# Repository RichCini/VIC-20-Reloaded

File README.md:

# VIC-20-Reloaded
Reimaging of the original VIC-20cr ("cost-reduced") main board in a smaller footprint based
on schmetics of the 251027-01D version as redrawn by Steve Gray. This should represent
changes through ECO 830151 as of 4/12/1983.

## Introduction
This project is a re-implementation of a VIC-20 based on the cost-reduced version from 1983.
It's built using commonly-existing TTL (all of the original types of chips used are still 
generally available) and original core chips from a VIC-20 (the CPU, VIAs, VIC, and original
mask ROMs) which were typically socketed. The memory chips (2114L and 6116), which are not
typically socketed, are still available as used or new-old-stock. 

## How is this version similar?
Since it's based on the original schematics, it's identical operationally and 99% identical
electrically (except as noted in the next section). I also tried to keep the parts placement
relationally similar to the original, recognizing that the board size is different. Parts 
designators are the same.

## How is this version different?
### Size
My main goal was to reimplement the VIC in a smaller form factor. I was able to squeeze it
{mostly} into an S-100 format (which is 10" x 5"; actual is 10.375" x 5.375") size. As such,
this board isn't a drop-in replacement. However, the spacing and placement of the side 
(power/joystick) and the rear (expansion cartridge, video, serial IEC) are
placed at the correct distances from the upper-right corner.

### Ports
Due to the smaller form factor, the cassette port was eliminated (instead opting for a 
6-pin header for an external driver) and the user port was moved to the left side. The 
orientation of the expansion connector was changed to vertical (more like the Atari 2600
which saved about 2" of board space). Using the expansion connector is limited to one
cartridge, or an expansion board that uses two pieces connected by a cable (there is
another repro here that has an example).

### Power
Electrically, I opted for a single 5V power supply (9VAC wasn't needed as there is no
cassette port), and the power switch is slightly different due to parts availability.
The main fuse holder is different, but the same 5x20mm fuse is used. Large axial
capacitor was replaced with smaller radial cap of the same value.

### Other
Since the board is autorouted to a smaller footprint, circuit paths and keepout
areas are different from the original.

## Versions
* v1.0-001: Initial prototype based on original schematic; screen artifacts
* v1.1-001: Second prototype with a rearranged chip layout; screen artifacts.
* v1.1-002: Third prototype. A transcription error was found in the original schematic.  
            Corrected. Works.
* v1.1-002E: Final version.

## Known Bugs
Current Release (1.1-002E):
* The signal flag "S01" was incorrectly used for the CPU PHI1 output. The system works
  with this improperly connected signal, but the fix is to lift pins UE10.3 and UC3.3
  and connect them with a jumper. The way the traces are routed make it hard to make a
  single-cut fix.

Prior Release (1.1-002D): 
* An error was introduced in this version as a result of rearranging the data bus lines
  lines on IC UF8 (74LS245). D4 (pin 4) and D5 (pin 5) were reversed. There is a picture
  (ECO_001) which indicates a convenient place to cut two traces and cross-wire them.
  Will be fixed in the next version.

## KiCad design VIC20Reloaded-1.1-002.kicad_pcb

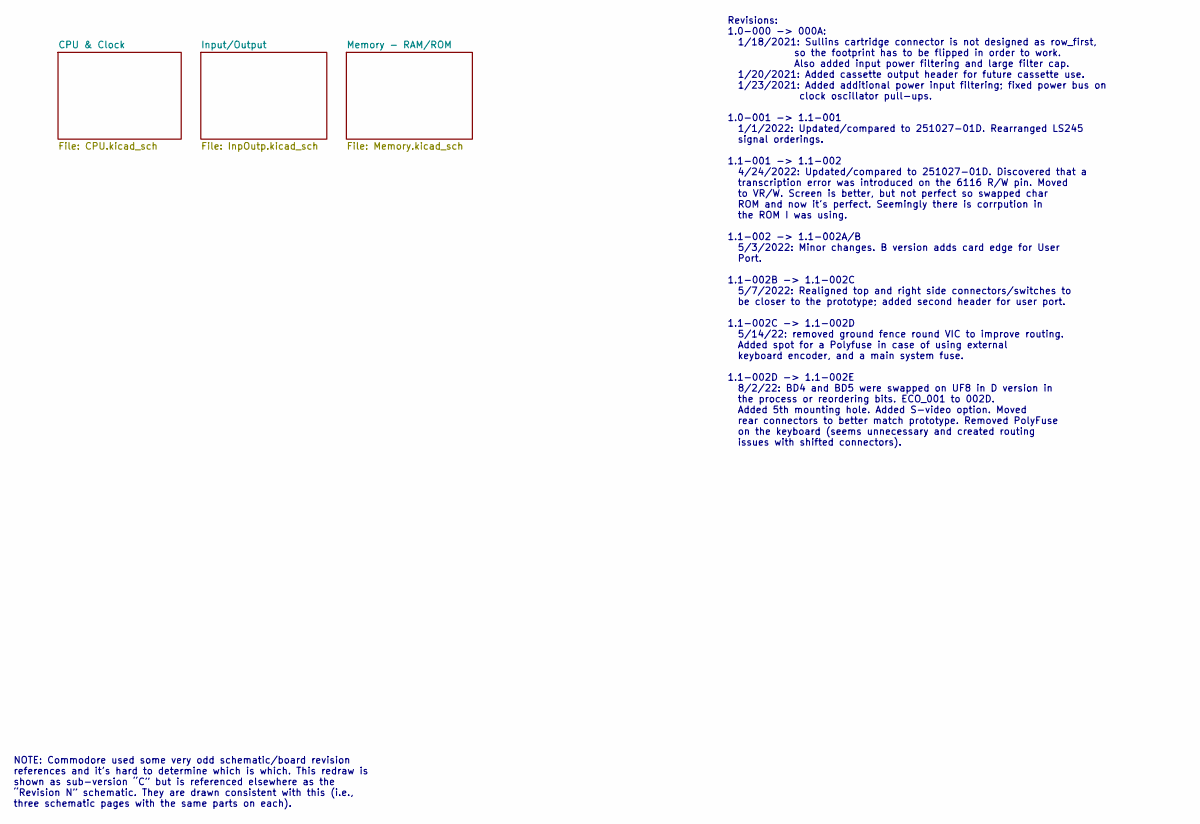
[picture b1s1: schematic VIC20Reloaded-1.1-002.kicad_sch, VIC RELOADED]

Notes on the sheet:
NOTE: Commodore used some very odd schematic/board revision references and it’s hard to determine which is which. This redraw is shown as sub-version “C” but is referenced elsewhere as the “Revision N” schematic. They are drawn consistent with this (i.e., three schematic pages with the same parts o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
Revisions: 1.0-000 -> 000A: 1/18/2021: Sullins cartridge connector is not designed as row_first, so the footprint has to be flipped in order to work. Also added input power filtering and large filter cap. 1/20/2021: Added cassette output header for future cassette use. 1/23/2021: Added additional p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

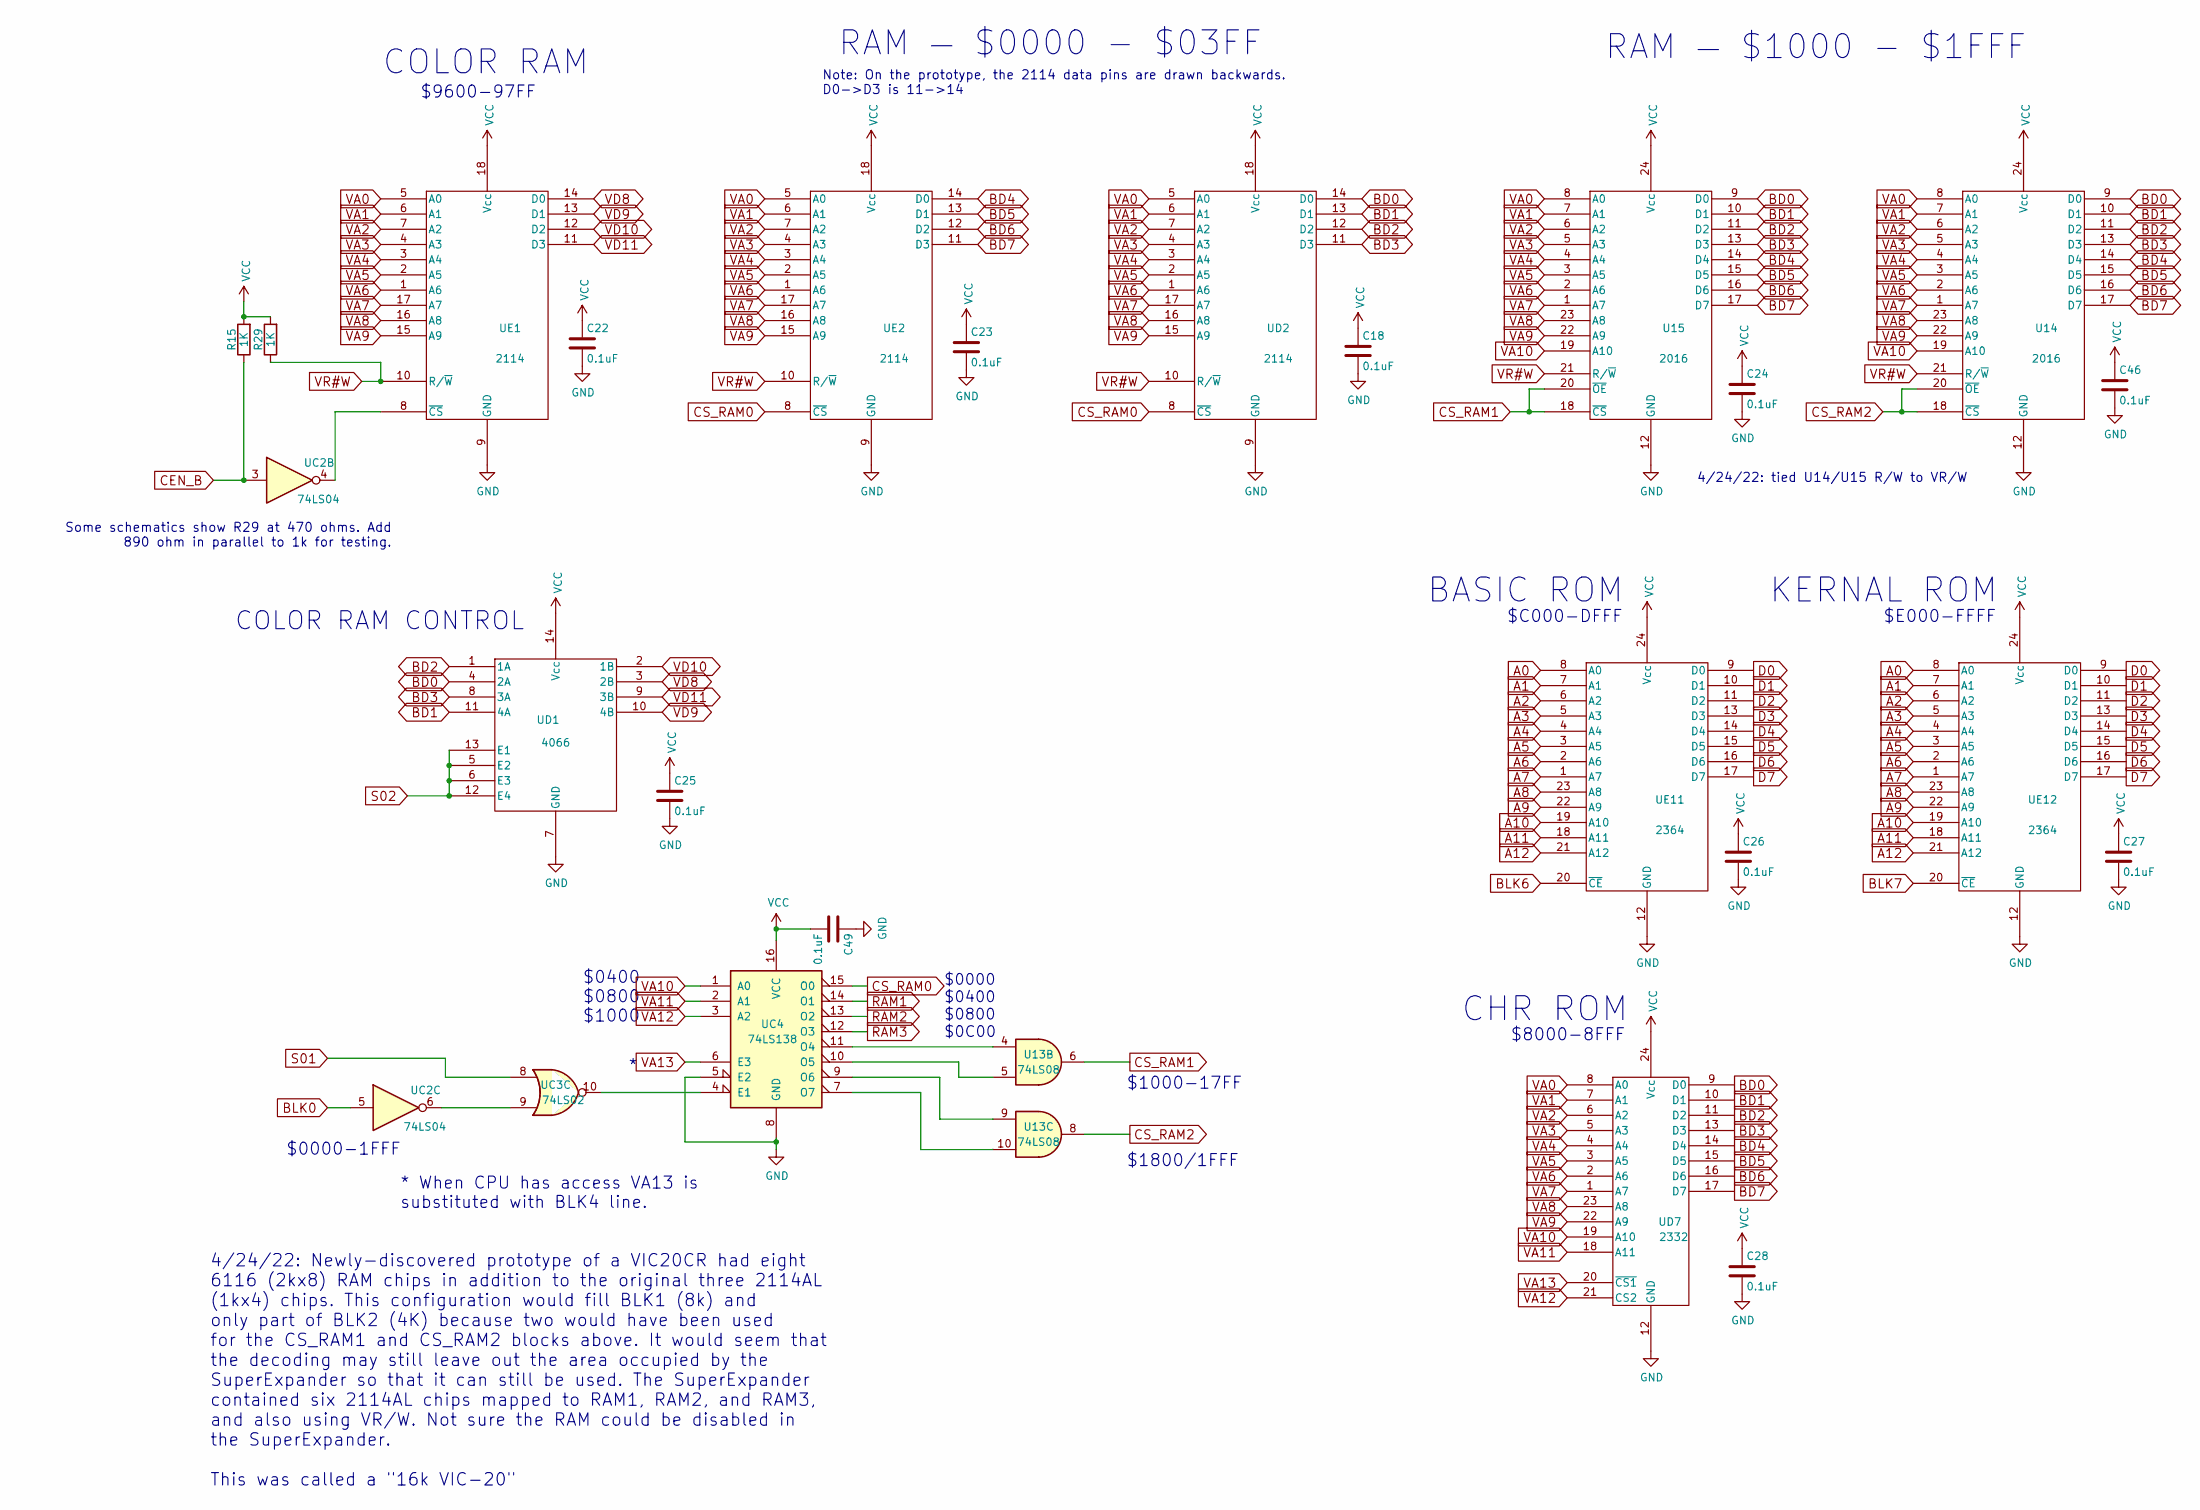
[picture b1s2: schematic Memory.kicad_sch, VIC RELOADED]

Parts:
C18, C22, C23, C24, C25, C26, C27, C28, C46, C49: 0.1uF; C_Disc_D4.3mm_W1.9mm_P5.00mm
R15, R29: 1K; R_Axial_DIN0207_L6.3mm_D2.5mm_P7.62mm_Horizontal
U13: 74LS08; DIP-14_W7.62mm_Socket
U14, U15: 2016; DIP-24_W15.24mm_Socket
UC2: 74LS04; DIP-14_W7.62mm_Socket
UC3: 74LS02; DIP-14_W7.62mm_Socket
UC4: 74LS138; DIP-16_W7.62mm_Socket
UD1: 4066; DIP-14_W7.62mm_Socket
UD2: 2114; DIP-18_W7.62mm_Socket
UD7: 2332; DIP-24_W15.24mm_Socket
UE1, UE2: 2114; DIP-18_W7.62mm_Socket
UE11, UE12: 2364; DIP-24_W15.24mm_Socket

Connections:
A0: UE11.8 (A0), UE12.8 (A0); also elsewhere on the board
A1: UE11.7 (A1), UE12.7 (A1); also elsewhere on the board
A2: UE11.6 (A2), UE12.6 (A2); also elsewhere on the board
A3: UE11.5 (A3), UE12.5 (A3); also elsewhere on the board
A4: UE11.4 (A4), UE12.4 (A4); also elsewhere on the board
A5: UE11.3 (A5), UE12.3 (A5); also elsewhere on the board
A6: UE11.2 (A6), UE12.2 (A6); also elsewhere on the board
A7: UE11.1 (A7), UE12.1 (A7); also elsewhere on the board
A8: UE11.23 (A8), UE12.23 (A8); also elsewhere on the board
A9: UE11.22 (A9), UE12.22 (A9); also elsewhere on the board
A10: UE11.19 (A10), UE12.19 (A10); also elsewhere on the board
A11: UE11.18 (A11), UE12.18 (A11); also elsewhere on the board
A12: UE11.21 (A12), UE12.21 (A12); also elsewhere on the board
BD0: U14.9 (D0), U15.9 (D0), UD1.4 (2A), UD2.14 (D0), UD7.9 (D0); also elsewhere on the board
BD1: U14.10 (D1), U15.10 (D1), UD1.11 (4A), UD2.13 (D1), UD7.10 (D1); also elsewhere on the board
BD2: U14.11 (D2), U15.11 (D2), UD1.1 (1A), UD2.12 (D2), UD7.11 (D2); also elsewhere on the board
BD3: U14.13 (D3), U15.13 (D3), UD1.8 (3A), UD2.11 (D3), UD7.13 (D3); also elsewhere on the board
BD4: U14.14 (D4), U15.14 (D4), UD7.14 (D4), UE2.14 (D0); also elsewhere on the board
BD5: U14.15 (D5), U15.15 (D5), UD7.15 (D5), UE2.13 (D1); also elsewhere on the board
BD6: U14.16 (D6), U15.16 (D6), UD7.16 (D6), UE2.12 (D2); also elsewhere on the board
BD7: U14.17 (D7), U15.17 (D7), UD7.17 (D7), UE2.11 (D3); also elsewhere on the board
BLK0: UC2.5; also elsewhere on the board
BLK6: UE11.20 (~CE); also elsewhere on the board
BLK7: UE12.20 (~CE); also elsewhere on the board
CEN_B: R15.1, UC2.3; also elsewhere on the board
CS_RAM0: UC4.15 (O0), UD2.8 (~CS), UE2.8 (~CS)
CS_RAM1: U13.6, U15.18 (~CS), U15.20 (~OE)
CS_RAM2: U13.8, U14.18 (~CS), U14.20 (~OE)
D0: UE11.9 (D0), UE12.9 (D0); also elsewhere on the board
D1: UE11.10 (D1), UE12.10 (D1); also elsewhere on the board
D2: UE11.11 (D2), UE12.11 (D2); also elsewhere on the board
D3: UE11.13 (D3), UE12.13 (D3); also elsewhere on the board
D4: UE11.14 (D4), UE12.14 (D4); also elsewhere on the board
D5: UE11.15 (D5), UE12.15 (D5); also elsewhere on the board
D6: UE11.16 (D6), UE12.16 (D6); also elsewhere on the board
D7: UE11.17 (D7), UE12.17 (D7); also elsewhere on the board
GND: C18.2, C22.2, C23.2, C24.2, C25.2, C26.2, C27.2, C28.2, C46.2, C49.1, U14.12 (GND), U15.12 (GND), UC4.5 (E2), UC4.8 (GND), UD1.7 (GND), UD2.9 (GND), UD7.12 (GND), UE1.9 (GND), UE2.9 (GND), UE11.12 (GND), UE12.12 (GND); also elsewhere on the board
unnamed: U13.4, UC4.11 (O4)
unnamed: U13.5, UC4.10 (O5)
unnamed: U13.9, UC4.9 (O6)
unnamed: U13.10, UC4.7 (O7)
unnamed: UC2.4, UE1.8 (~CS)
unnamed: UC2.6, UC3.9
unnamed: UC3.10, UC4.4 (E1)
RAM1: UC4.14 (O1); also elsewhere on the board
RAM2: UC4.13 (O2); also elsewhere on the board
RAM3: UC4.12 (O3); also elsewhere on the board
S01: UC3.8; also elsewhere on the board
S02: UD1.5 (E2), UD1.6 (E3), UD1.12 (E4), UD1.13 (E1); also elsewhere on the board
VA0: U14.8 (A0), U15.8 (A0), UD2.5 (A0), UD7.8 (A0), UE1.5 (A0), UE2.5 (A0); also elsewhere on the board
VA1: U14.7 (A1), U15.7 (A1), UD2.6 (A1), UD7.7 (A1), UE1.6 (A1), UE2.6 (A1); also elsewhere on the board
VA2: U14.6 (A2), U15.6 (A2), UD2.7 (A2), UD7.6 (A2), UE1.7 (A2), UE2.7 (A2); also elsewhere on the board
VA3: U14.5 (A3), U15.5 (A3), UD2.4 (A3), UD7.5 (A3), UE1.4 (A3), UE2.4 (A3); also elsewhere on the board
VA4: U14.4 (A4), U15.4 (A4), UD2.3 (A4), UD7.4 (A4), UE1.3 (A4), UE2.3 (A4); also elsewhere on the board
VA5: U14.3 (A5), U15.3 (A5), UD2.2 (A5), UD7.3 (A5), UE1.2 (A5), UE2.2 (A5); also elsewhere on the board
VA6: U14.2 (A6), U15.2 (A6), UD2.1 (A6), UD7.2 (A6), UE1.1 (A6), UE2.1 (A6); also elsewhere on the board
VA7: U14.1 (A7), U15.1 (A7), UD2.17 (A7), UD7.1 (A7), UE1.17 (A7), UE2.17 (A7); also elsewhere on the board
VA8: U14.23 (A8), U15.23 (A8), UD2.16 (A8), UD7.23 (A8), UE1.16 (A8), UE2.16 (A8); also elsewhere on the board
VA9: U14.22 (A9), U15.22 (A9), UD2.15 (A9), UD7.22 (A9), UE1.15 (A9), UE2.15 (A9); also elsewhere on the board
VA10: U14.19 (A10), U15.19 (A10), UC4.1 (A0), UD7.19 (A10); also elsewhere on the board
VA11: UC4.2 (A1), UD7.18 (A11); also elsewhere on the board
VA12: UC4.3 (A2), UD7.21 (CS2); also elsewhere on the board
VA13: UC4.6 (E3), UD7.20 (~CS1); also elsewhere on the board
VCC: C18.1, C22.1, C23.1, C24.1, C25.1, C26.1, C27.1, C28.1, C46.1, C49.2, R15.2, R29.2, U14.24 (Vcc), U15.24 (Vcc), UC4.16 (VCC), UD1.14 (Vcc), UD2.18 (Vcc), UD7.24 (Vcc), UE1.18 (Vcc), UE2.18 (Vcc), UE11.24 (Vcc), UE12.24 (Vcc); also elsewhere on the board
VD8: UD1.3 (2B), UE1.14 (D0); also elsewhere on the board
VD9: UD1.10 (4B), UE1.13 (D1); also elsewhere on the board
VD10: UD1.2 (1B), UE1.12 (D2); also elsewhere on the board
VD11: UD1.9 (3B), UE1.11 (D3); also elsewhere on the board
VR#W: R29.1, U14.21 (R/~W), U15.21 (R/~W), UD2.10 (R/~W), UE1.10 (R/~W), UE2.10 (R/~W); also elsewhere on the board

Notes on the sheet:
$9600-97FF
4/24/22: Newly-discovered prototype of a VIC20CR had eight 6116 (2kx8) RAM chips in addition to the original three 2114AL (1kx4) chips. This configuration would fill BLK1 (8k) and only part of BLK2 (4K) because two would have been used for the CS_RAM1 and CS_RAM2 blocks above. It would seem that th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
$8000-8FFF
COLOR RAM CONTROL
$0000 $0400 $0800 $0C00
$0000-1FFF
KERNAL ROM
$0400 $0800 $1000
Note: On the prototype, the 2114 data pins are drawn backwards. D0->D3 is 11->14
* When CPU has access VA13 is substituted with BLK4 line.
COLOR RAM
CHR ROM
$C000-DFFF
4/24/22: tied U14/U15 R/W to VR/W
RAM — $1000 - $1FFF
BASIC ROM
$E000-FFFF
$1000-17FF $1800/1FFF
Some schematics show R29 at 470 ohms. Add 890 ohm in parallel to 1k for testing.
RAM — $0000 - $03FF

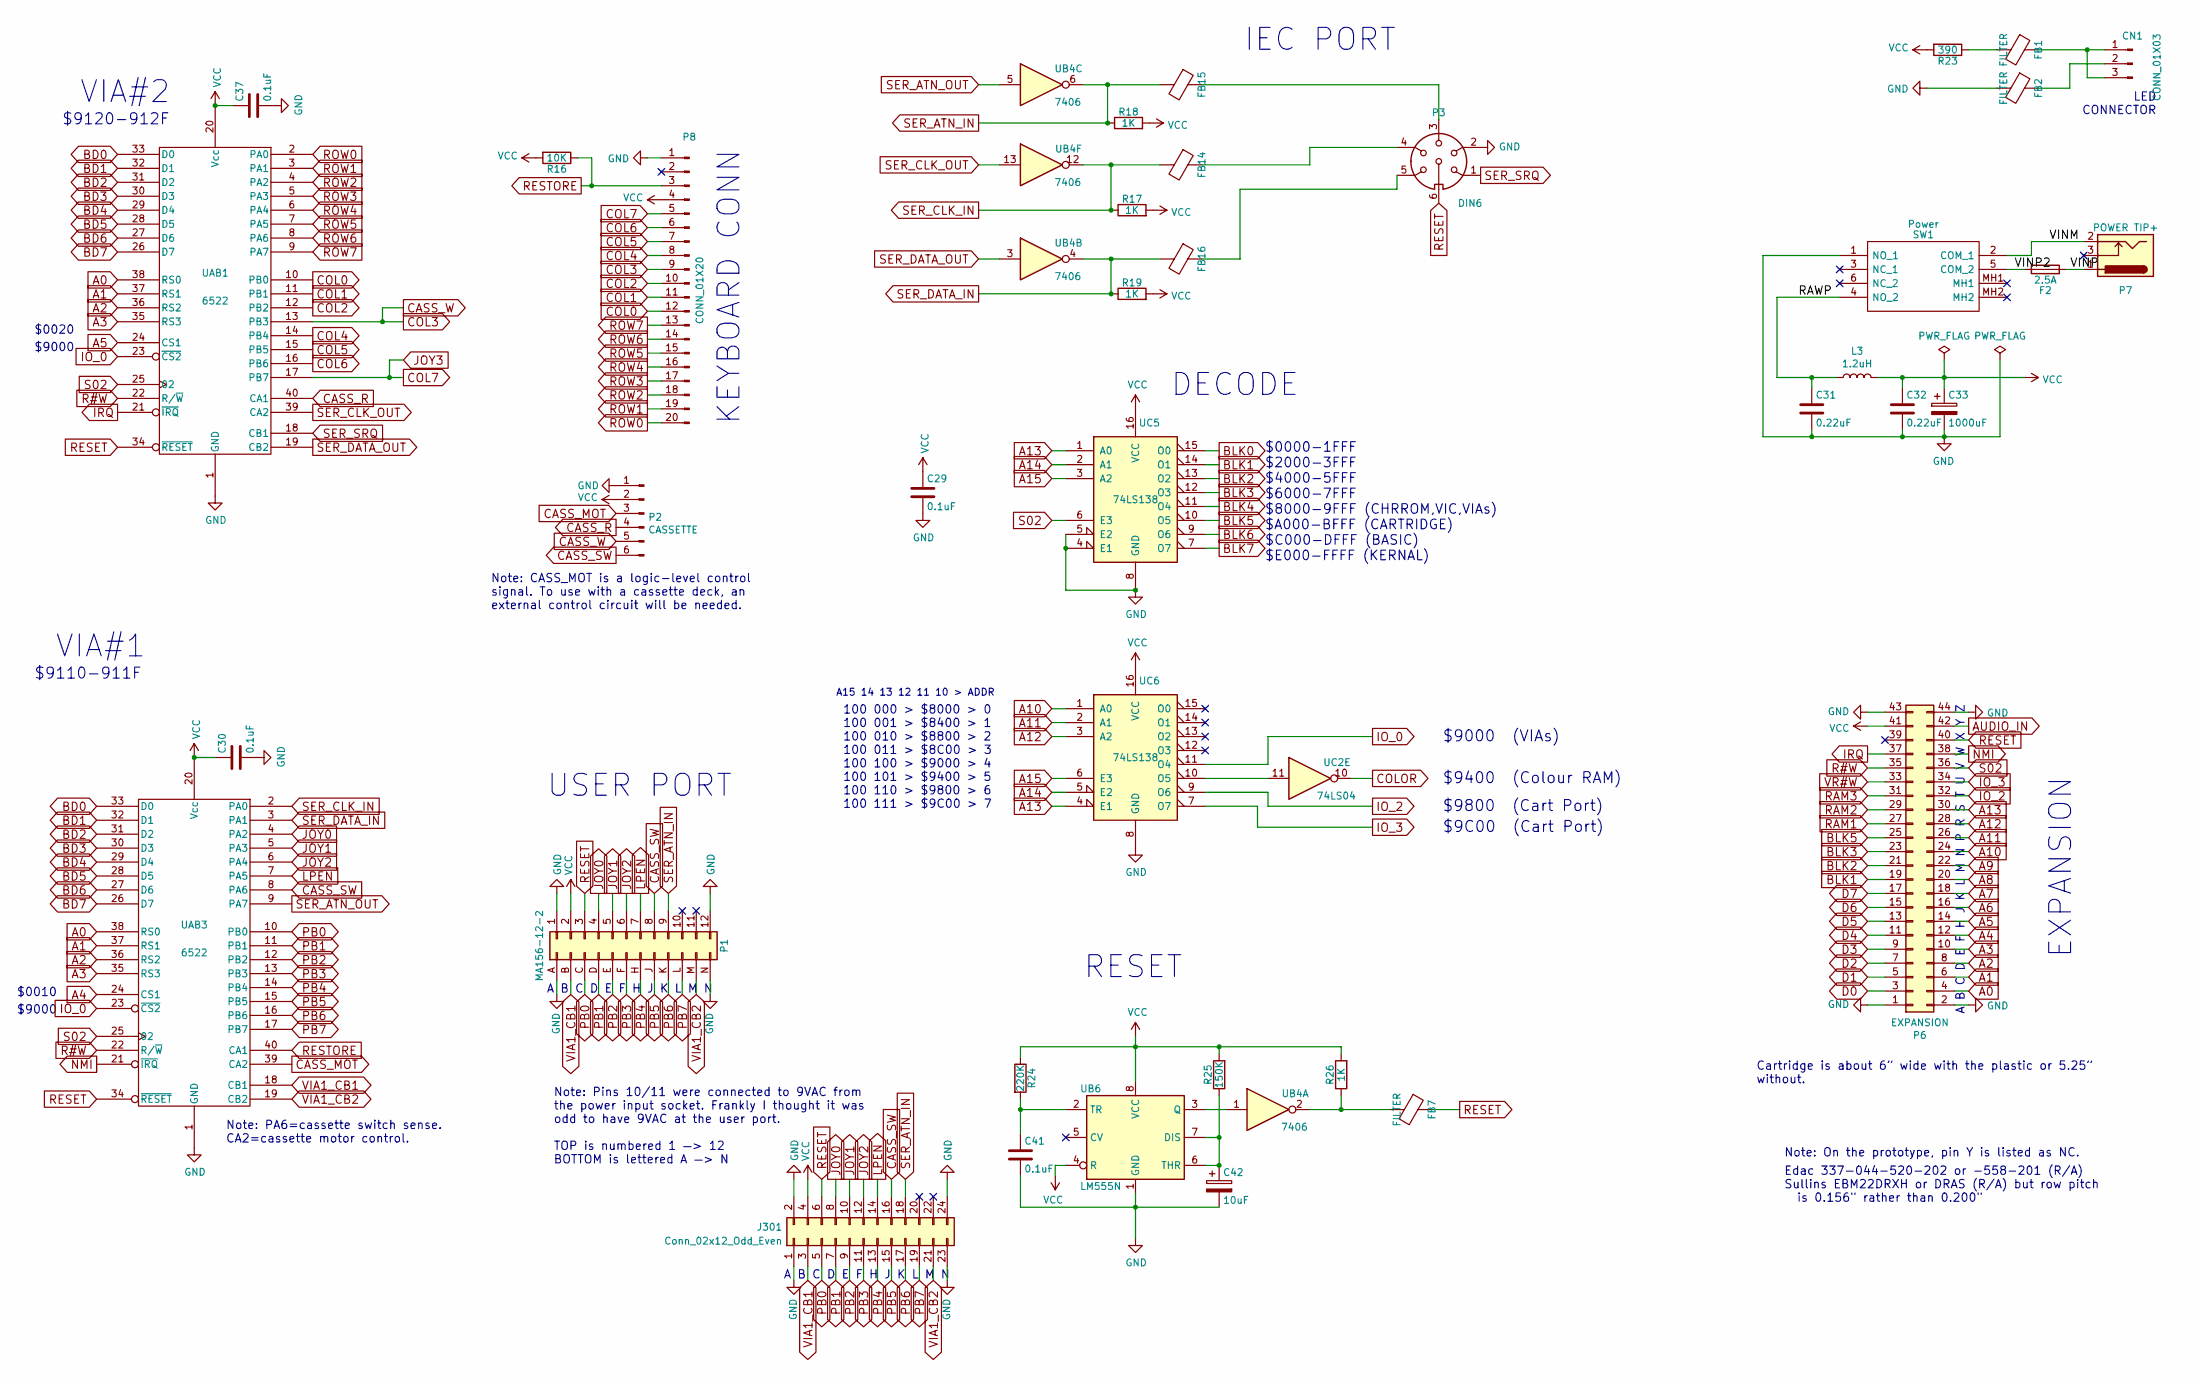
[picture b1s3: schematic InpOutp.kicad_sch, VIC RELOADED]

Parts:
C29, C30, C37, C41: 0.1uF; C_Disc_D4.3mm_W1.9mm_P5.00mm
C31, C32: 0.22uF; C_Disc_D4.3mm_W1.9mm_P5.00mm
C33: 1000uF; CP_Radial_D10.0mm_P5.00mm
C42: 10uF; CP_Radial_D4.0mm_P1.50mm
CN1: CONN_01X03; PinHeader_1x03_P2.54mm_Vertical
F2: 2.5A; FUSE_4527
FB1, FB2: FILTER; L_Axial_L7.0mm_D3.3mm_P2.54mm_Vertical_Fastron_MICC
FB7, FB14, FB15, FB16: FILTER; L_Axial_L7.0mm_D3.3mm_P10.16mm_Horizontal_Fastron_MICC
J301: Conn_02x12_Odd_Even; PinHeader_2x12_P2.54mm_Vertical
L3: 1.2uH; L_Axial_L7.0mm_D3.3mm_P10.16mm_Horizontal_Fastron_MICC
P1: MA156-12-2
P2: CASSETTE; PinHeader_1x06_P2.54mm_Vertical
P3: DIN6; CUI_SDS-60J
P6: EXPANSION; Sullins_02_22_Card_Edge_Connector
P7: POWER TIP+; BarrelJack_Horizontal
P8: CONN_01X20; PinHeader_1x20_P2.54mm_Vertical
R16: 10K; R_Axial_DIN0207_L6.3mm_D2.5mm_P7.62mm_Horizontal
R17, R18, R19, R26: 1K; R_Axial_DIN0207_L6.3mm_D2.5mm_P7.62mm_Horizontal
R23: 390; R_Axial_DIN0207_L6.3mm_D2.5mm_P7.62mm_Horizontal
R24: 220K; R_Axial_DIN0207_L6.3mm_D2.5mm_P7.62mm_Horizontal
R25: 150K; R_Axial_DIN0207_L6.3mm_D2.5mm_P7.62mm_Horizontal
SW1: Power; M2022TXW41DA
UAB1, UAB3: 6522; DIP-40_W15.24mm_Socket
UB4: 7406; DIP-14_W7.62mm_Socket
UB6: LM555N; DIP-8_W7.62mm_Socket
UC2: 74LS04; DIP-14_W7.62mm_Socket
UC5, UC6: 74LS138; DIP-16_W7.62mm_Socket

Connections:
/Input/Output/RAWP: C31.1, L3.1, SW1.4 (NO_2)
/Input/Output/VINM: P7.2, SW1.2 (COM_1)
/Input/Output/VINP: F2.2, P7.1
/Input/Output/VINP2: F2.1, SW1.5 (COM_2)
A0: P6.4, UAB1.38 (RS0), UAB3.38 (RS0); also elsewhere on the board
A1: P6.6, UAB1.37 (RS1), UAB3.37 (RS1); also elsewhere on the board
A2: P6.8, UAB1.36 (RS2), UAB3.36 (RS2); also elsewhere on the board
A3: P6.10, UAB1.35 (RS3), UAB3.35 (RS3); also elsewhere on the board
A4: P6.12, UAB3.24 (CS1); also elsewhere on the board
A5: P6.14, UAB1.24 (CS1); also elsewhere on the board
A6: P6.16; also elsewhere on the board
A7: P6.18; also elsewhere on the board
A8: P6.20; also elsewhere on the board
A9: P6.22; also elsewhere on the board
A10: P6.24, UC6.1 (A0); also elsewhere on the board
A11: P6.26, UC6.2 (A1); also elsewhere on the board
A12: P6.28, UC6.3 (A2); also elsewhere on the board
A13: P6.30, UC5.1 (A0), UC6.4 (E1); also elsewhere on the board
A14: UC5.2 (A1), UC6.5 (E2); also elsewhere on the board
A15: UC5.3 (A2), UC6.6 (E3); also elsewhere on the board
AUDIO_IN: P6.42; also elsewhere on the board
BD0: UAB1.33 (D0), UAB3.33 (D0); also elsewhere on the board
BD1: UAB1.32 (D1), UAB3.32 (D1); also elsewhere on the board
BD2: UAB1.31 (D2), UAB3.31 (D2); also elsewhere on the board
BD3: UAB1.30 (D3), UAB3.30 (D3); also elsewhere on the board
BD4: UAB1.29 (D4), UAB3.29 (D4); also elsewhere on the board
BD5: UAB1.28 (D5), UAB3.28 (D5); also elsewhere on the board
BD6: UAB1.27 (D6), UAB3.27 (D6); also elsewhere on the board
BD7: UAB1.26 (D7), UAB3.26 (D7); also elsewhere on the board
BLK0: UC5.15 (O0); also elsewhere on the board
BLK1: P6.19, UC5.14 (O1); also elsewhere on the board
BLK2: P6.21, UC5.13 (O2); also elsewhere on the board
BLK3: P6.23, UC5.12 (O3); also elsewhere on the board
BLK4: UC5.11 (O4); also elsewhere on the board
BLK5: P6.25, UC5.10 (O5); also elsewhere on the board
BLK6: UC5.9 (O6); also elsewhere on the board
BLK7: UC5.7 (O7); also elsewhere on the board
CASS_MOT: P2.3, UAB3.39 (CA2)
CASS_R: P2.4, UAB1.40 (CA1)
CASS_SW: J301.16, P1.8, P2.6, UAB3.8 (PA6)
CASS_W: P2.5, P8.9, UAB1.13 (PB3)
COL0: P8.12, UAB1.10 (PB0)
COL1: P8.11, UAB1.11 (PB1)
COL2: P8.10, UAB1.12 (PB2)
COL4: P8.8, UAB1.14 (PB4)
COL5: P8.7, UAB1.15 (PB5)
COL6: P8.6, UAB1.16 (PB6)
COL7: P8.5, UAB1.17 (PB7); also elsewhere on the board
COLOR: UC2.10; also elsewhere on the board
D0: P6.3; also elsewhere on the board
D1: P6.5; also elsewhere on the board
D2: P6.7; also elsewhere on the board
D3: P6.9; also elsewhere on the board
D4: P6.11; also elsewhere on the board
D5: P6.13; also elsewhere on the board
D6: P6.15; also elsewhere on the board
D7: P6.17; also elsewhere on the board
GND: C29.2, C30.2, C31.2, C32.2, C33.2, C37.2, C41.2, C42.2, FB2.2, J301.1, J301.2, J301.23, J301.24, P1.1, P1.12, P1.A, P1.N, P2.1, P3.2, P6.1, P6.2, P6.43, P6.44, P8.1, SW1.1 (NO_1), UAB1.1 (GND), UAB3.1 (GND), UB6.1 (GND), UC5.4 (E1), UC5.5 (E2), UC5.8 (GND), UC6.8 (GND); also elsewhere on the board
IO_0: UAB1.23 (~CS2), UAB3.23 (~CS2), UC6.11 (O4)
IO_2: P6.32, UC6.9 (O6); also elsewhere on the board
IO_3: P6.34, UC6.7 (O7); also elsewhere on the board
IRQ: P6.37, UAB1.21 (~IRQ); also elsewhere on the board
JOY0: J301.8, P1.4, UAB3.4 (PA2); also elsewhere on the board
JOY1: J301.10, P1.5, UAB3.5 (PA3); also elsewhere on the board
JOY2: J301.12, P1.6, UAB3.6 (PA4); also elsewhere on the board
LPEN: J301.14, P1.7, UAB3.7 (PA5); also elsewhere on the board
NMI: P6.38, UAB3.21 (~IRQ); also elsewhere on the board
unnamed: C41.1, R24.2, UB6.2 (TR)
unnamed: C42.1, R25.1, UB6.6 (THR), UB6.7 (DIS)
unnamed: CN1.1, CN1.3, FB1.1
unnamed: CN1.2, FB2.1
unnamed: FB1.2, R23.1
unnamed: FB7.2, R26.1, UB4.2
unnamed: FB14.1, P3.4
unnamed: FB15.1, P3.3
unnamed: FB16.1, P3.5
unnamed: UB4.1, UB6.3 (Q)
unnamed: UC2.11, UC6.10 (O5)
PB0: J301.5, P1.C, UAB3.10 (PB0)
PB1: J301.7, P1.D, UAB3.11 (PB1)
PB2: J301.9, P1.E, UAB3.12 (PB2)
PB3: J301.11, P1.F, UAB3.13 (PB3)
PB4: J301.13, P1.H, UAB3.14 (PB4)
PB5: J301.15, P1.J, UAB3.15 (PB5)
PB6: J301.17, P1.K, UAB3.16 (PB6)
PB7: J301.19, P1.L, UAB3.17 (PB7)
R#W: P6.35, UAB1.22 (R/~W), UAB3.22 (R/~W); also elsewhere on the board
RAM1: P6.27; also elsewhere on the board
RAM2: P6.29; also elsewhere on the board
RAM3: P6.31; also elsewhere on the board
RESET: FB7.1, J301.6, P1.3, P3.6, P6.40, UAB1.34 (~RESET), UAB3.34 (~RESET); also elsewhere on the board
RESTORE: P8.3, R16.1, UAB3.40 (CA1)
ROW0: P8.20, UAB1.2 (PA0)
ROW1: P8.19, UAB1.3 (PA1)
ROW2: P8.18, UAB1.4 (PA2)
ROW3: P8.17, UAB1.5 (PA3)
ROW4: P8.16, UAB1.6 (PA4)
ROW5: P8.15, UAB1.7 (PA5)
ROW6: P8.14, UAB1.8 (PA6)
ROW7: P8.13, UAB1.9 (PA7)
S02: P6.36, UAB1.25 (02), UAB3.25 (02), UC5.6 (E3); also elsewhere on the board
SER_ATN_IN: FB15.2, J301.18, P1.9, R18.1, UB4.6
SER_ATN_OUT: UAB3.9 (PA7), UB4.5
SER_CLK_IN: FB14.2, R17.1, UAB3.2 (PA0), UB4.12
SER_CLK_OUT: UAB1.39 (CA2), UB4.13
SER_DATA_IN: FB16.2, R19.1, UAB3.3 (PA1), UB4.4
SER_DATA_OUT: UAB1.19 (CB2), UB4.3
SER_SRQ: P3.1, UAB1.18 (CB1)
VCC: C29.1, C30.1, C32.1, C33.1, C37.1, J301.4, L3.2, P1.2, P2.2, P6.41, P8.4, R16.2, R17.2, R18.2, R19.2, R23.2, R24.1, R25.2, R26.2, UAB1.20 (Vcc), UAB3.20 (Vcc), UB6.4 (R), UB6.8 (VCC), UC5.16 (VCC), UC6.16 (VCC); also elsewhere on the board
VIA1_CB1: J301.3, P1.B, UAB3.18 (CB1)
VIA1_CB2: J301.21, P1.M, UAB3.19 (CB2)
VR#W: P6.33; also elsewhere on the board

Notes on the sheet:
EXPANSION
Cartridge is about 6” wide with the plastic or 5.25” without.
DECODE
RESET
Note: PA6=cassette switch sense. CA2=cassette motor control.
A B C D E F H J K L M N P R S T U V W X Y Z
A B C D E F H J K L M N
$9000
Note: Pins 10/11 were connected to 9VAC from the power input socket. Frankly I thought it was odd to have 9VAC at the user port. TOP is numbered 1 —> 12 BOTTOM is lettered A —> N
IEC PORT
$9C00 (Cart Port)
$9120-912F
Note: On the prototype, pin Y is listed as NC.
LED CONNECTOR
$9400 (Colour RAM)
$9000 (VIAs)
$9800 (Cart Port)
KEYBOARD CONN
Edac 337-044-520-202 or -558-201 (R/A) Sullins EBM22DRXH or DRAS (R/A) but row pitch is 0.156" rather than 0.200"
$0010
USER PORT
$9110-911F
100 000 > $8000 > 0 100 001 > $8400 > 1 100 010 > $8800 > 2 100 011 > $8C00 > 3 100 100 > $9000 > 4 100 101 > $9400 > 5 100 110 > $9800 > 6 100 111 > $9C00 > 7
A15 14 13 12 11 10 > ADDR
Note: CASS_MOT is a logic-level control signal. To use with a cassette deck, an external control circuit will be needed.
VIA#2
$0020
$0000-1FFF $2000-3FFF $4000-5FFF $6000-7FFF $8000-9FFF (CHRROM,VIC,VIAs) $A000-BFFF (CARTRIDGE) $C000-DFFF (BASIC) $E000-FFFF (KERNAL)
VIA#1

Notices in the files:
VIC20Reloaded-1.1-002.kicad_pcb:
Copyright (c) 2022 Richard Cini. All Rights reserved.
Copyright (c) 2022 Steve Gray and Richard A. Cini.
All Rights Reserved. Licensed for hobbyist use only.
